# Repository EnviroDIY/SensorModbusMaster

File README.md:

# SensorModbusMaster<!--! {#mainpage} -->

This library is designed to use an Arduino as a Modbus master to communicate with a sensor/slave via the [Modbus RTU](https://en.wikipedia.org/wiki/Modbus) communication protocol.
It's specifically written with lots of "higher-level" functions to help out users who are largely unfamiliar with the Modbus protocol and want an easy way to get information from a Modbus device.

<!--! @tableofcontents -->

<!--! @m_footernavigation -->

<!--! @if GITHUB -->

- [SensorModbusMaster](#sensormodbusmaster)
  - [Using the library](#using-the-library)
  - [Modbus Maps](#modbus-maps)
  - [Supported Data Types](#supported-data-types)
  - [The TAI64 Timestamp Format](#the-tai64-timestamp-format)
  - [Notes on TTL and RS485/RS322 electrical communications standards](#notes-on-ttl-and-rs485rs322-electrical-communications-standards)
  - [Hardware interface suggestions for EnviroDIY Mayfly](#hardware-interface-suggestions-for-envirodiy-mayfly)
  - [Library installation](#library-installation)

<!--! @endif -->
_____

## Using the library

To communicate with a Modbus sensor or other Modbus slave, first create a stream instance (ie, Serial1, SoftwareSerial, AltSoftSerial) and then an instance of the modbusMaster.

```cpp
// Create the stream instance
HardwareSerial modbusSerial = Serial1;  // ALWAYS use HardwareSerial if it's an option
// OR
// AltSoftSerial modbusSerial;  // AltSoftSerial should be your second choice, if your board is supported
// OR
// SoftwareSerial modbusSerial(txPin, rxPin);  // SoftwareSerial should be your last choice.

// Create the modbus instance
modbusMaster modbus;
```

Within the setup function begin both the serial instance and the modbusMaster instance.
The enable pin allows you to use an RS485 to TTL adapter that is half-duplex with a pin that enables data sending.

```cpp
// Start the stream
modbusSerial.begin(baudRate);

// start the modbus
modbus.begin(modbusSlaveID, modbusSerial);
// ^^ use this if you have an RS485 adapter with automatic flow control
// modbus.begin(modbusSlaveID, modbusSerial, enablePin);
// ^^ use this if you need to manually control flow direction on your RS485 adapter
```

Once you've created and begun these, getting data from or adding data to a register is very simple:

```cpp
// Retrieve data from a read-only input register
// Input registers are called with 0x04 - Input registers are always read-only
// This gets a 32-bit big endian float from input register 15
modbus.float32FromRegister(0x04, 15, bigEndian);

// Retrieve data from a read/write holding register
// Holding registers are called with 0x03
// Retrieve a signed 16-big endian float from holding register 12
modbus.int16FromRegister(0x03, 12, littleEndian);

// Write the value "56" to holding register 20 as a little-endian unsigned 16-bit integer
modbus.uint16ToRegister(20, 56, littleEndian);
```

_____

## Modbus Maps

While Modbus RTU specifications define the format of a data frame and a very simple data structure for a master and slave, there are no specification for what types of data a slave stores, where it is stored, or in what format it is stored.
You **MUST** get this information from the manufacturer/programmer of your Modbus device.
Typically this information is shared in what is called a Modbus map.

You need the following data from your Modbus map:

- the baud rate the device communicates at (Modbus allows any baud rate)
- the parity the device uses on the serial line (Modbus technically allows 8O1, 8E1, and 8N2, though some devices may use 8N1)
  - Software serial libraries generally do not support 8O1, 8E1, or 8N2; you will need a hardware serial port available if your device uses one of these stop/parity configurations
- the type of register or coils the data you are interested is stored in (ie, holding register, input register, coil, or discrete input)
  - Note - This library does not currently support getting or setting values in coils.
  - All input registers are read-only.
If your map says a register is read/write (R/W), it is a holding register.
- the register or coil number the data is stored in
- the format of data within the registers/coils (ie, float, integer, bit mask, ascii text)
- whether multi-register numeric data is stored as ["big-endian" or "little-endian"](https://en.wikipedia.org/wiki/Endianness) values (That is, is it high _word_ first or low _word_ first.
There are no specifications for this.)
- whether single-register data is stored "big-endian" or "little-endian" (That is, is it high _byte_ first or low _byte_ first.
Modbus specifies that it should be high byte first (big-endian), but devices vary.)
  - Note - This library only supports data that is "fully" big or little endian.
That is, data must be both high byte and high word first or both low byte and low word first.
Mixed endianness is not supported.

Without this information, you have little hope of being able to communicate properly with the device.
You can use programs like [CAS Modbus scanner](http://www.chipkin.com/cas-modbus-scanner/) to find a device if its address, baud rate, and parity are unknown, but it may take some time to make a connection.
You can also use the "scanRegisters" utility in this library to get a view of all the registers, but if you don't have a pretty good idea of what you are looking for that will not be as helpful as you might hope.
_____

## Supported Data Types

The following data types are supported:

- `uint16` (16-bit unsigned integer)
  - Value must be within a single 16-bit register
  - bigEndian or littleEndian can be specified, bigEndian will be used by default
  - By default, the Modbus command for pre-setting a single register will be used (0x06).
Set the forceMultiple boolean flag to 'true' to force the use of the Modbus command for setting multiple resisters (0x10).
- `int16` (16-bit signed integer)
  - Value must be within a single 16-bit register
  - bigEndian or littleEndian can be specified, bigEndian will be used by default
  - By default, the Modbus command for pre-setting a single register will be used (0x06).
Set the forceMultiple boolean flag to 'true' to force the use of the Modbus command for setting multiple resisters (0x10).
- `float32` (32-bit float)
  - Value must be in two adjacent 16-bit registers
  - bigEndian or littleEndian can be specified, bigEndian will be used by default
  - Only "fully" big or little endianness is supported - that is both high byte and high word first or both low byte and low word first.
- `uint32` (32-bit unsigned integer)
  - Value must be in two adjacent 16-bit registers
  - bigEndian or littleEndian can be specified, bigEndian will be used by default
  - Only "fully" big or little endianness is supported - that is both high byte and high word first or both low byte and low word first.
- `int32` (32-bit signed integer)
  - Value must be in two adjacent 16-bit registers
  - bigEndian or littleEndian can be specified, bigEndian will be used by default
  - Only "fully" big or little endianness is supported - that is both high byte and high word first or both low byte and low word first.
- **TAI64** (64-bit timestamp)
  - Value must be in four contiguous 16-bit registers
  - Value is always fully big endian
  - Supported as if it were a 32-bit unix timestamp because the first 32-bits of the TAI64 timestamp will be 0x40000000 until the year 2106.
- **TAI64N** (64-bit timestamp followed by a 32-bit nanosecond count)
  - Value must be in six contiguous 16-bit registers
  - Value is always fully big endian
  - Note that the seconds and nanoseconds are broken into two different fields.
- **TAI64NA** (64-bit timestamp followed by a 32-bit nanosecond count and then a 32-bit attosecond count)
  - Value must be in eight contiguous 16-bit registers
  - Value is always fully big endian
  - Note that the seconds, nanoseconds, and attoseconds are broken into three different fields.
- `byte` (8-bit unsigned integer or raw byte of data)
  - Must specify either the first or second 8-bit component of a single 16-bit register)
  - By default, the Modbus command for pre-setting a single register will be used (0x06).
Set the forceMultiple boolean flag to 'true' to force the use of the Modbus command for setting multiple resisters (0x10).
- `char` (c++/ASCII style characters)
  - Characters can be in one or more contiguous 16-bit registers
  - Length of the character array must be specified
  - By default, the Modbus command for pre-setting a single register will be used (0x06) if the character array has two or fewer characters.
Set the forceMultiple boolean flag to 'true' to force the use of the Modbus command for setting multiple resisters (0x10).
- `String` (Arduino Strings)
  - Characters can be in one or more contiguous 16-bit registers
  - By default, the Modbus command for pre-setting a single register will be used (0x06) if the String has two or fewer characters.
Set the forceMultiple boolean flag to 'true' to force the use of the Modbus command for setting multiple resisters (0x10).
- **pointer** (pointers to other registers)
  - Value must be within a single 16-bit register
  - By default, the Modbus command for pre-setting a single register will be used (0x06).
Set the forceMultiple boolean flag to 'true' to force the use of the Modbus command for setting multiple resisters (0x10).

There are also mid-level functions available to help to reduce serial traffic by calling many registers at once and low level functions to make raw Modbus calls.
See SensorModbusMaster.h for all the available functions and their required and optional inputs
_____

## The TAI64 Timestamp Format

Within this library, the support for TAI64, TAI64N and TAI64NA has these
limitations:

- The time value must be in four (TAI64), six (TAI64N), or eight (TAI64NA)
contiguous 16-bit registers
- The time value must always be fully big endian
- The full 64-bit timestamp is cropped to 32-bits and only the lower 32-bits are
used as if it was a 32-bit unix timestamp.
  - The upper 32-bits of the TAI64 timestamp will be 0x40000000 until the year 2106.

> TAI stands for Temps Atomique International, the current international
> real-time standard.

> TAI64 defines a 64-bit integer format where each value identifies a particular
> SI second. The duration of SI seconds is defined through a count of state
> transitions of the cesium atom and understood as constant. Time is structured
> as a sequence of seconds anchored on the start of the year 1970 in the
> Gregorian calendar, when atomic time (TAI) became the international standard
> for real time. The standard defines 262 seconds before the year 1970, and
> another 262 from this epoch onward, thus covering a span of roughly 300 billion
> years, enough for most applications.

> The extensions TAI64N and TAI64NA allow for finer time resolutions by
> referring to particular nanoseconds and attoseconds (10-18 s), respectively,
> within a particular second.

The defining paper: [Toward a Unified Timestamp with explicit precision](https://www.demographic-research.org/volumes/vol12/6/12-6.pdf)

[An excellent (and easier to read) explanation of the TAI64 formats on Stack Overflow](https://stackoverflow.com/questions/50907211/what-is-a-tai64-time-format)

_____

## Notes on TTL and RS485/RS322 electrical communications standards

While Modbus RTU specifications define the format of a data frame transferred over a serial line, the type of serial signal is not defined.
Many Modbus sensors communicate over [RS-485](https://en.wikipedia.org/wiki/RS-485).
To interface between RS485 and the TTL used by standard Arduino-type boards, you will need an RS485-to-TTL adapter. There are a number of RS485-to-TTL adapters available.
When shopping for one, be mindful of the logic level of the TTL output by the adapter.
The MAX485, one of the most popular adapters, has a 5V logic level in the TTL signal.
This will _fry_ any board that can only use on 3.3V logic.
You would need a voltage shifter in between the Mayfly and the MAX485 to make it work.
Also note that most RS485-to-TTL adapters are implemented _without_ automatic flow control.
That is, you must manually set voltages on driver enable and receiver enable pins to control the data flow direction.
While this library includes functions for setting the enables, I've found commutation to be much more stable on adapters with built-in flow control.
You will also need a [hardware interface board](#hardware-interface-suggestions-for-envirodiy-mayfly) to communicate between an Arduino and any Modbus sensor that communicates over [RS422](https://en.wikipedia.org/wiki/RS-422) or [RS232](https://en.wikipedia.org/wiki/RS-232).
Again, mind your voltages and the method of direction control.

## Hardware interface suggestions for EnviroDIY Mayfly

For use with the [EnviroDIY Mayfly data logger](https://github.com/EnviroDIY/EnviroDIY_Mayfly_Logger) and other Arduino framework boards, you will likely need some additional [Hardware for using ModbusRTU with RS-485 on Arduino](https://github.com/EnviroDIY/SensorModbusMaster/tree/master/hardware).

We have developed a [Modbus-Mayfly-WingShield](https://github.com/EnviroDIY/SensorModbusMaster/tree/master/hardware/Modbus-Mayfly_WingShield) that combines AltSoftSerial TTL to RS-485 conversion with an optional power boost to 9V or 12V.
This has worked quite well for us for a variety of deployment configurations and sensors.

## Library installation

This library is available through both the Arduino and PlatformIO library registries.
[Here is the PlatformIO registry page.](https://registry.platformio.org/libraries/envirodiy/SensorModbusMaster)
Use the Arduino IDE to find the library in that registry.
The build and ingest logs for this library into the Arduino library registry are available [here](https://downloads.arduino.cc/libraries/logs/github.com/EnviroDIY/SensorModbusMaster/).

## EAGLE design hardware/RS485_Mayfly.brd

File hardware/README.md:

# Hardware for using ModbusRTU with RS-485 on Arduino<!--! {#page_hardware} -->

> [!NOTE]
> Hardware designs have been moved to the [Mayfly-Modbus-Wing](https://github.com/EnviroDIY/Mayfly-Modbus-Wing) repo!

## Why Modbus Hardware is Required for Arduino

The [Modbus RTU](https://en.wikipedia.org/wiki/Modbus) *logical* communication protocol is typically transmitted using the *physical* [RS-485](https://en.wikipedia.org/wiki/RS-485) serial communication signaling standard.

Arduino-framework micro-controllers, on the other hand, transmit serial signals using transistor-to-transistor logic, or [TTL serial](https://learn.sparkfun.com/tutorials/serial-communication/wiring-and-hardware).

Therefore, most sensors using this library will need to an RS485-to-TTL adapter module to communicate. Also, most Modbus sensors require 5-12V of power, so a separate step-up power converter may be necessary to run it off a 3.3V Arduino micro-controller. Last, the electrical "logic level" signals returned from a sensor will typically have a HIGH (or "1") returned at the same voltage that powers the sensor, which means that a logic-level shifter/converter is required to ensure that communication signals being received by the Arduino micro-controller are 3.3V. Luckily, most RS485-to-TTL adapter modules also perform logic-level voltage conversions.

For all these reasons, additional hardware is usually required to interface a Modbus sensor with an Arduino micro-controller.

We have developed some guidance, designs and documentation different interface hardware solutions that have worked for us. This information is now available in the [EnviroDIY/Mayfly-Modbus-Wing](https://github.com/EnviroDIY/Mayfly-Modbus-Wing) repo.

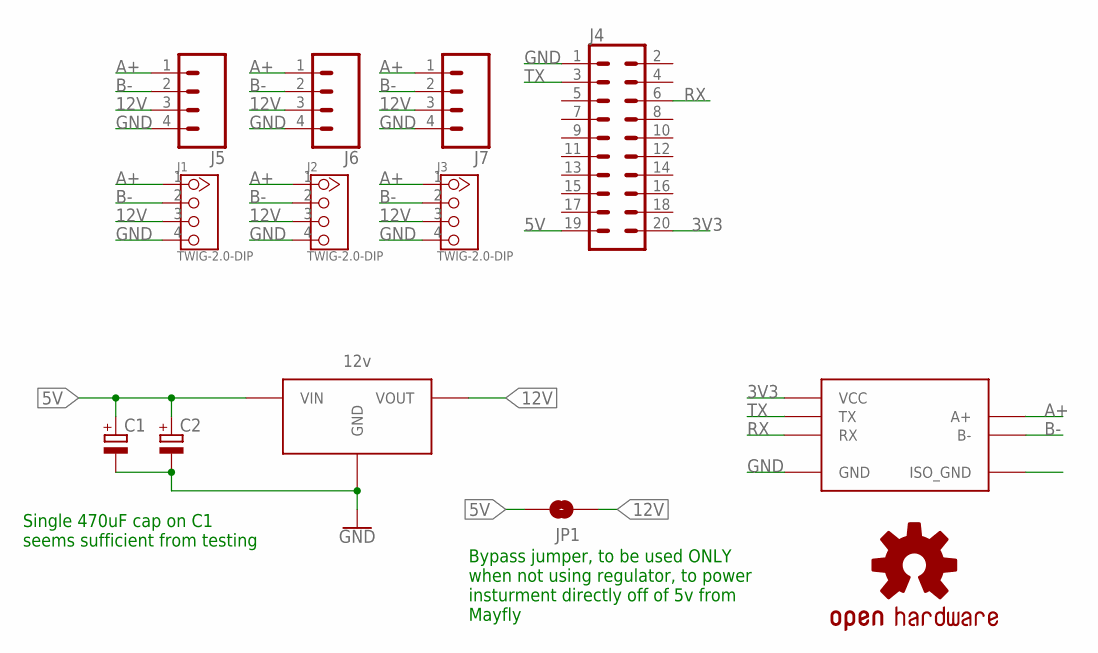
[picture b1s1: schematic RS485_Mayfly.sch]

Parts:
C1, C2: CPOL-EUE2,5-6E; E2,5-6E
J1, J2, J3: TWIG-2.0-DIP; 2.0_1X4
J4: CONN_10X2; 2X10
J5, J6, J7: CONN_42.54_NOSILK; 1X04_NOSILK
JP1: JUMPER-SMT_2_NO_SILK; SMT-JUMPER_2_NO_SILK
LOGO1: OSHW-LOGOMINI; OSHW-LOGO-MINI
U$1: 12v; POLOLU_REG
U$2: SMC_RS485

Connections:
3V3: J4.20, U$2.VCC
5V: C1.+, C2.+, J4.19, JP1.2, U$1.VIN
12V: J1.3, J2.3, J3.3, J5.3, J6.3, J7.3, JP1.1, U$1.VOUT
A+: J1.1, J2.1, J3.1, J5.1, J6.1, J7.1, U$2.A+
B-: J1.2, J2.2, J3.2, J5.2, J6.2, J7.2, U$2.B-
GND: C1.-, C2.-, J1.4, J2.4, J3.4, J4.1, J5.4, J6.4, J7.4, U$1.GND, U$2.GND
RX: J4.6, U$2.RX
TX: J4.3, U$2.TX

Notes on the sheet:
Bypass jumper, to be used ONLY when not using regulator, to power insturment directly off of 5v from Mayfly
Single 470uF cap on C1 seems sufficient from testing

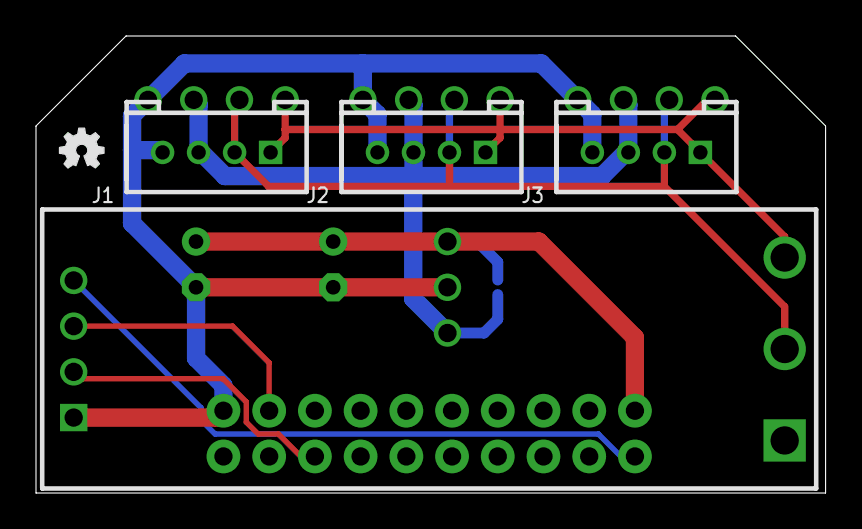
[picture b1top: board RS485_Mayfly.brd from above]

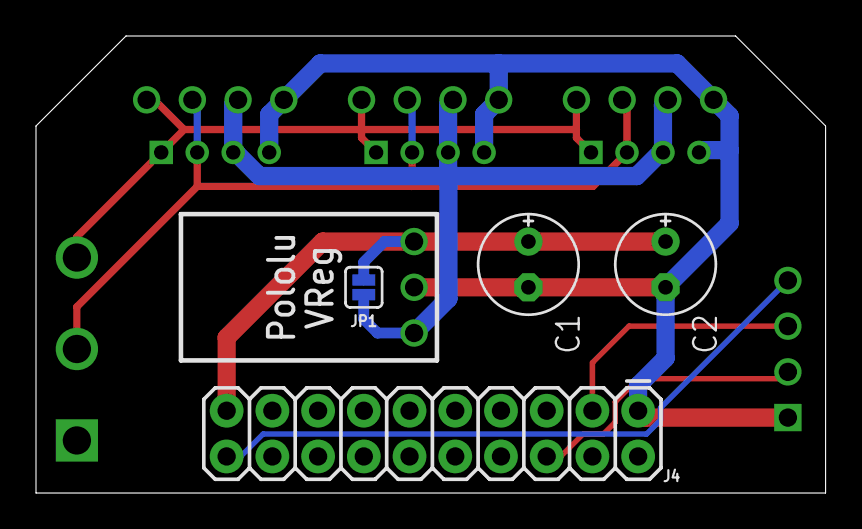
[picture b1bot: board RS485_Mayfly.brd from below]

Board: 2 copper layers, 43.9 x 25.4 mm, 13 parts (5 on the bottom side), 8 nets.

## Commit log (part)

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2017-08-15 Added some basic modbus functions taken from Yosemitech library
2017-08-15 Beginning to write up the supported functions
2017-08-15 Now getting basic responses!
2017-08-15 Data from frame is currently wrong
2017-08-16 setup fro holding registers seems to work
2017-08-17 Attempting to simplify to function overload
2017-08-17 Probably made more complex by attempting to simplify
2017-08-17 Added (untested) functions to set values
2017-08-17 tweek
2017-08-17 Added input register setup calls
2017-08-17 Send commands are working now
2017-08-17 Starting in on parameter metadata
2017-08-18 Getvalues functions and some rearranging
2017-08-18 Changed command order of dataFromFrame
2017-08-18 Just moved chuinks of code
2017-08-18 Rearranging
    Replaced the overloaded (ugly) dataFromFrame with many functions that return specific types basec on the name.
    Also moved all of the printing about setup, etc, to the printSetup function
2017-08-18 Now actually compiles
2017-08-19 All *seems* to work
2017-08-21 New shortcut functions
2017-08-30 Renamed getValues to getParameterValues
    Also starting to get ready to read spectral data
2017-08-30 More fxns named
2017-09-05 Added library files, got headers working
2017-09-06 Stripped from scanModbus into its own modbus lib
2017-09-06 Fixed keywords, removed s::can register log
2017-09-06 Update version for release
2017-09-06 Made the responseBuffer public
2017-09-06 Fixed example
2017-09-06 Added higher level functions to set registers
2017-09-06 Renamed functions for setting registers
2017-09-06 Populated functions for adding data to a frame
2017-09-06 Bumped version
2017-09-07 Fixed functions to empty buffers
2017-09-18 Added check that string values are printable characters
2017-09-18 Deleted incomplete, failing example
2017-09-21 Another tweak for unprintable characters
2017-09-21 Fixed TAI64FromRegister
    Also renamed some internal arguiments for my own confusion-avoidance.
2017-09-21 Added a real ReadMe
2017-09-21 Added link to CAS modbus scanner
2017-09-21 Still working on issue with uprintable strings
2017-09-22 Fixed 0 to '\0' (null)
2017-10-09 Receiver enable in begin fxn
2017-11-21 Update to ReadMe and examples
2017-11-21 Added TAI64N and TAI64NA
2017-11-21 Fixed tai64 sizes
2017-11-22 *Really* fixed the TAI64
2018-01-12 Updated library keywords
2018-01-23 Update library.properties
    added `paragraph=` to avoid error raised by issue #4
2018-01-31 Fix to force multiple
2018-01-31 Fixed bug in setting multiple registers
2018-02-02 Added extra serial buffer clear
2018-02-02 Fixed read-me typos, bumped version
2018-02-06 Registered examples in library.json
2018-03-28 Initial commit to Hardware branch
    @bschulz1701
2018-03-28 Added PCB companies to ReadMe
2018-04-02 Added board and schematic images
    Added PNGs for both the PCB and the schematic for the Mrk1 design, adjusted noted in schematic design as well
2018-07-19 Update ReadMe, Moved hardware docs; added photos
    photos of Modbus-Mayfly_WingShield
2018-09-13 Updating Hardware Docs. Modbus-Mayfly-WingShield
    Addressing both #3 & #5
2018-09-13 Updates to Modbus-Mayfly-WingShield readme
    #3
2018-09-13 Fixes to Modbus-Mafly-WingShield Readme
    #3
2018-09-18 Updated part numbers on WingShield
    Added part numbers in the Eagle file for the capacitors and connectors on the WIngShield, still need to add full BOM for system eventually
2019-08-29 Fix attoseconds, -Wextra warnings
2019-12-04 Typo in a comment
2019-12-10 0 is an allowable pin number, slightly clearer debug message
2019-12-10 Version bump
2019-12-10 Faster switch-back to receiver enable
2019-12-12 Critical bug fix for NULL pointer https://github.com/EnviroDIY/SensorModbusMaster/issues/11
2020-01-07 Minor changes to ReadMe, added example
2020-01-17 Reference/pointer change for M0
2020-01-17 Skip the NRF for now
2020-08-21 Create IMG_2174+TerminationResistor.jpg
    For #14
2021-02-05 a release for discussion
2021-02-05 add https://github.com/neilh10/SensorModbusMaster/issues/1
2021-02-05 add circuitHub output - https://github.com/neilh10/SensorModbusMaster/issues/1
2021-02-05 added 12V fuse. added ground planes to PCB and did nortons analysis on critical ground currents. https://github.com/neilh10/SensorModbusMaster/issues/1
2021-02-11 Rev4 final - sent to oshPark for initial test build Added docs and kicad files https://github.com/neilh10/SensorModbusMaster/issues/1
2021-03-10 Added rev6 schematic
2021-03-25 kicad archive and rev6 BOM
2021-05-21 Complete hardware spin-off
    Deleting hardware files, now that all have been spun off to https://github.com/EnviroDIY/Mayfly-Modbus-Wing.
    Completes issue #8
2022-08-24 Update readWriteRegister.ino
    changed main loop function comment from main setup to main loop
2024-05-30 Changed debug print
2024-05-30 Prepare for Doxygen
2024-05-30 Fix example name
2024-05-30 Fix some renames
2024-05-30 clang format
2024-05-30 Fixed spelling of receive and pin int type
2024-05-30 Bucketloads of documentation!
2024-05-31 More documentation updates
2024-05-31 Add author
2024-05-31 Add some missed docs for enums
2024-06-03 update links
2024-06-05 Fix debug, again
2024-06-05 Switch to reusable workflows
2024-06-05 add version tags to reusable workflows
2024-06-05 Update build docs
2024-06-05 Add inputs to verify lib structure
2024-06-05 Update changelog
2024-06-05 Fix some board names
2024-06-05 Can't exclude home, remove unused scripts
2024-06-05 Update gitignore
2024-06-05 No ESP32C6 for now
2024-06-06 Update readme tags for latest doxygen
2024-06-06 Backfill changelog, bump version
2024-06-06 Update doxygen tags post merge
2024-06-06 Use svg for dot
2024-06-08 Add dot fontname/size
2024-06-08 Fix non-int dot font size
2024-06-08 Adjust workflow conditionals
2024-06-08 Give inputs to prepare release
2024-06-09 Fix version tag
2024-06-09 Remove v from changelog numbers
2024-06-09 deploy: e6b6888cf6fb25a65b3d8bd4c72b008ae59ea5c2
2024-06-11 Fix tags in changelog, typos in docs
2024-06-11 Add logos
2024-06-17 Don't create dot graphs ignored by m.css
2024-06-17 Add clipboard
2024-06-18 No DOT
2024-06-18 deploy: 193104e116bf659bc665f60e757e21a0a3855152
2024-06-19 Minor docs updates
2024-06-19 deploy: 0a4e4d935ed1dd398b7efecacfc8aedea9c2d23a
2024-06-21 Update testing for more processors
2024-06-24 Wait for checks before release
2024-06-25 Fix tag on wait workflow [ci skip]
2024-06-25 Fix workflow arg name [ci skip]
2024-06-25 Don't wait on workflow dispatches [ci skip]
2024-06-25 Fix broken release workflow [ci skip]
2024-06-25 add workflow_run trigger for buid docs [ci skip]
2024-06-25 deploy: 7c48fb4bf224c80387ed7acd58e398e8bddb68fc
2024-09-12 Return write fuction to readWriteRegister.ino example
    To previous functionality. Note that in commit f1daa2fdd22c7ec991fc2ff50330aa41e4a7a53e I made fixes to this example to get it to work with AltSoftSerial, similar to those made in YosemitechModbus wi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
2024-09-12 Add getSetAddress.ino example #30
    This a functional first step, but want to flesh out a bit further.
2024-09-16 Update getSetAddress.ino
    Improvements toward #30
2024-09-16 Cleanup getSetAddress example
    #30
2024-09-17 Version bump to 0.7.3
    I forgot to update these with release of 0.7.2
2024-09-24 Update dependabot and changelog header
2025-08-11 ci: bump ArcticLampyrid/action-wait-for-workflow from 1.2.0 to 1.3.0
    Bumps [ArcticLampyrid/action-wait-for-workflow](https://github.com/arcticlampyrid/action-wait-for-workflow) from 1.2.0 to 1.3.0.
    - [Release notes](https://github.com/arcticlampyrid/action-wait-for-workflow/releases)
    - [Commits](https://github.com/arcticlampyrid/action-wait-for-workflow/compare/v1.2.0...v1.3.0)
    ---
    updated-dependencies:
    - dependency-name: ArcticLampyrid/action-wait-for-workflow
2025-08-18 ci: bump actions/checkout from 4 to 5
    Bumps [actions/checkout](https://github.com/actions/checkout) from 4 to 5.
    - [Release notes](https://github.com/actions/checkout/releases)
    - [Changelog](https://github.com/actions/checkout/blob/main/CHANGELOG.md)
    - [Commits](https://github.com/actions/checkout/compare/v4...v5)
    ---
    updated-dependencies:
2025-08-18 Added cspell config, fix spelling errors
2025-08-18 Remove return type in doxygen return command
2025-08-18 Added coil commands, separate input/holding commands, commands to user buffer
2025-08-18 Add example dependencies file; update gitignore
2025-08-18 Update documentation workflow
2025-08-18 Remove extra default value
2025-08-18 Don't build AltSoftSerial by default in examples
2025-08-18 Force software serial for Uno
2025-08-18 Bump actions/checkout
2025-08-18 deploy: 39f12b7a51b8f7cde422670b5f0aa337d0f5fb66
2025-08-18 Bump wait for workflow
2025-08-18 Correct names of read only vs read write registers
2025-08-19 Added setters and getters for the enable pin, modbus command timeout, and modbus frame timeout
2025-08-19 deploy: 5cf26dd4aedb70d9b01a772ed2e4bd40e1e86883
2025-08-19 When dumping the buffer, wait the frame timeout time between characters instead of a set 1ms.
2025-08-19 deploy: 4134140e05ec5b98e90b639c15b459dec26f75fd
2025-08-20 Added extra functions specifying "holding" or "input" in the function name.
2025-08-20 Added the ability to change the number of times to retry commands.
2025-08-20 Remove inappropriate defaults in cpp
2025-08-20 Add a checkable error value and a more clear error response to sendCommand
2025-08-21 Fix error check in sendCommand
2025-08-21 Debugging change
2025-08-21 Use newer doxygen html comment config
2025-08-21 Fix fall-through
2025-08-21 debugging fix
2025-08-22 deploy: ee673c717af77f17ae2e745cae813a076730cb55
2025-08-22 Add note about library installation
2025-08-28 Fixed return value for sendCommand function
2025-08-28 Remove all variable length arrays
2025-08-28 deploy: 842ce2685852034710fcc9a7db42fe26a9503e4f
2025-08-28 Add more overloads, setters, getters
2025-08-28 More constructors
2025-08-28 deploy: 45630732817070b6342b909e03962c63cbd96aa5
2025-09-02 Removed slave id and many overloads
2025-09-02 Rename internal variables that confused me
2025-09-02 Remove references to slaveId
2025-09-02 Ensure send command always to specified slave
2025-09-02 Use getModbusData instead of getRegisters
2025-09-02 getRegisters/coils/inputs cannot use default buffer
2025-09-02 More pointer fixes
2025-09-02 Always specify source frame for fromFrame fxns
2025-09-02 Clarify destination in var name
2025-09-02 document missing params
2025-09-02 Fix some char pointers
2025-09-04 Re-allow response buffer as default; update some docs
2025-09-04 Re-Add the slave ID as a member
2025-09-04 Revert to the slave being a property which all commands use, rather than an argument to commands
2025-09-04 Support broadcast commands to address 0x0
2025-09-04 Re-Add all of the overloads
2025-09-04 deploy: 48f36a934b6ff3ad36df2289c3df9c66bdd60dd6
2025-09-08 Add debugging of slicing
2025-09-10 deploy: b652ec8129e1d7c1fa90986c1a93bde10da6b9b9
2025-09-10 null terminate all character strings
2025-09-10 deploy: 3602e86234ecad2404ca53e1571301f0c2a9d239
2025-09-11 Change byteToFrame, memset arrays to 0
2025-09-11 deploy: 333a27c811b159643e240e399bd705fa4ccb1c23
2025-09-11 Fix compiler warning
2025-09-11 deploy: ac223a9f261f27d93c1c0d94065d48f1f431bbbe
2025-09-12 Fixed attempt to print to nullptr
2025-09-12 deploy: 9bc2676d48ad6d84bb2a63d72964a62e79b86e96
2025-09-26 *Always* check that stream isn't null
2025-09-26 deploy: 68eb0cfe176895c377190dcad2242545e6a288d8
2025-10-27 Add an error for the wrong number of bytes returned
2025-10-27 Broadened use of improper response error
2025-10-27 deploy: c67b1039e5b404f42c911cd7c08ea4b4b36e87b4

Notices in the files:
parts and their libraries:
SparkFun-PowerSymbols: Licensing: Creative Commons ShareAlike 4.0 International - https://creativecommons.org/licenses/by-sa/4.0
